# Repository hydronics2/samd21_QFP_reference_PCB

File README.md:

# samd21_QFP_reference_PCB

This is a reference design for a SAMD21 for easy SWD programming and testing.  This layout should work with any SAMD21 QFP package. The QFP package is pretty easy to solder and gives you about the same amount of pins as the original Aruduino 328P. The following SAMD21 packages are QFP:
- SAMD21E15 32kB of Flash **(read this)
- SAMD21E16 64kB of flash **(read this)
- SAMD21E17 128kB of flash
- SAMD21E18 256kB of flash

I made a specific reference board for the SAMD21G [posted here](https://github.com/hydronics2/2020-samd21_QFP_Reference) used in the Adafruit ItsyBitsy M0.

I wanted to start to try SWD programming and these are the less expensive version of the popular SAMD21G on Adafruit and Sparkfun boards.
This PCB design relies heavily on Adafruit and Sparkfun reference design. I realized Adafruit has a similar design for their [32pin Trinket](https://learn.adafruit.com/assets/45723). They do not have a 32.768 crystal or a ferrite bead as recommended by Atmel. Not sure why/how that works. Instead of running the two pins PA00/PA01 to a crystal, they run them to their Dotstar LED!

You can order boards from Oshpark using this link: [project](https://oshpark.com/shared_projects/EjZP7lWQ)

Here's a list of parts:

- ATSAMD21E15B from [digikey](https://www.digikey.com/product-detail/en/microchip-technology/ATSAMD21E15B-AFT/1611-ATSAMD21E15B-AFTCT-ND/6832773). Don't get the ATSAMD21E15L!... the pinout is slightly different.
- generic 10 pin SWD Header from [mouser](https://www.mouser.com/ProductDetail/485-752)
- generic 5.08mm pitch screw headers (or 5mm)
- 	FIXED IND 10UH 500MA 300 MOHM [digikey](https://www.digikey.com/product-detail/en/tdk-corporation/MLZ2012N100LT000/445-6762-1-ND/2523583)
- 3.3V Regulator (18V max input) [mouser](https://www.mouser.com/ProductDetail/511-LDL1117S50R)
- T0-252-3 Mosfet (not needed) [mouser](https://www.mouser.com/ProductDetail/ON-Semiconductor-Fairchild/FDD8780?qs=%2fha2pyFadugI30EyIBTPkO8PumBRFL59Ls98N48NSzc%3d)
- USB micro connector [digikey](https://www.digikey.com/product-detail/en/amphenol-icc-fci/10118194-0001LF/609-4618-1-ND/2785382)
- standard 6mmx6mm tactile button [sparkfun](https://www.sparkfun.com/products/97)
- screw terminal 5mm pitch [sparkfun](https://www.sparkfun.com/products/8432) or [aliexpress](https://www.aliexpress.com/wholesale?catId=0&initiative_id=SB_20190221221755&SearchText=pcb+screw+terminal)
- input protection diodes on the 12V and USB input into the regulator. This is Adafruit's design. [digikey](https://www.digikey.com/product-detail/en/diodes-incorporated/B130-13-F/B130-FDICT-ND/815318)
- 32.768khz crystal (if needed, see above trinket design) [digikey](https://www.digikey.com/product-detail/en/epson/FC-135-32.7680KA-AG3/SER4086DKR-ND/6132726)
- crystal capacitors C7/C8 based on a 7pf load from the above crystal and assumed 2pf stray capacitence, CX1 = CX2 = 2(7pF - 2pF) = 10pF [digikey](https://www.digikey.com/product-detail/en/wurth-electronics-inc/885012006051/732-7793-1-ND/5454420)

SWD Programmer/Debugger: [Segger](https://www.digikey.com/product-detail/en/segger-microcontroller-systems/8.08.91-J-LINK-EDU-MINI/899-1061-ND/7387472)

Notes:
- add a ground plane
- chagne the silkscreen to SAMD21E15
- change the silkscreen C7/C8 from 15pf to 10pf

**READ THIS

The SAMD21E15 only has 32kb of flash. Fine for 8bit architecture but not for 32bit SAMD21 architecture!!
About 50 lines of simple code uses 332 bytes (12%) in for the UNO but compiles over 9,000 bytes (9248 bytes (56%)) for the SAMD21E15, SAMD21E16, SAMD21E17, etc

That means that I should have gone with the SAMD21E17 or SAMD21E18 with 128 or 256kb respectively.

[westf wrote this on the Arduino forum](https://forum.arduino.cc/index.php?topic=602377.msg4091161#msg4091161)... That's not as bad as it sounds - a sketch has a fair about of "fixed overhead" (an empty Zero sketch is 10k.)
So you're seeing THAT rather than some huge "50 lines of code bloats to 9k of code" multiplier for 32bit RISC.   You should be able to fit a pretty significant sketch into the 10k you have left...
But yeah, most ARM libraries (not just the Arduino code, BTW) pretty much assume that you'll have lots of memory, and don't bother being very inefficient.  (adding a tiny bit of floating point will use up another 9k.)
(and 8k for a bootloader?  Sheesh!)

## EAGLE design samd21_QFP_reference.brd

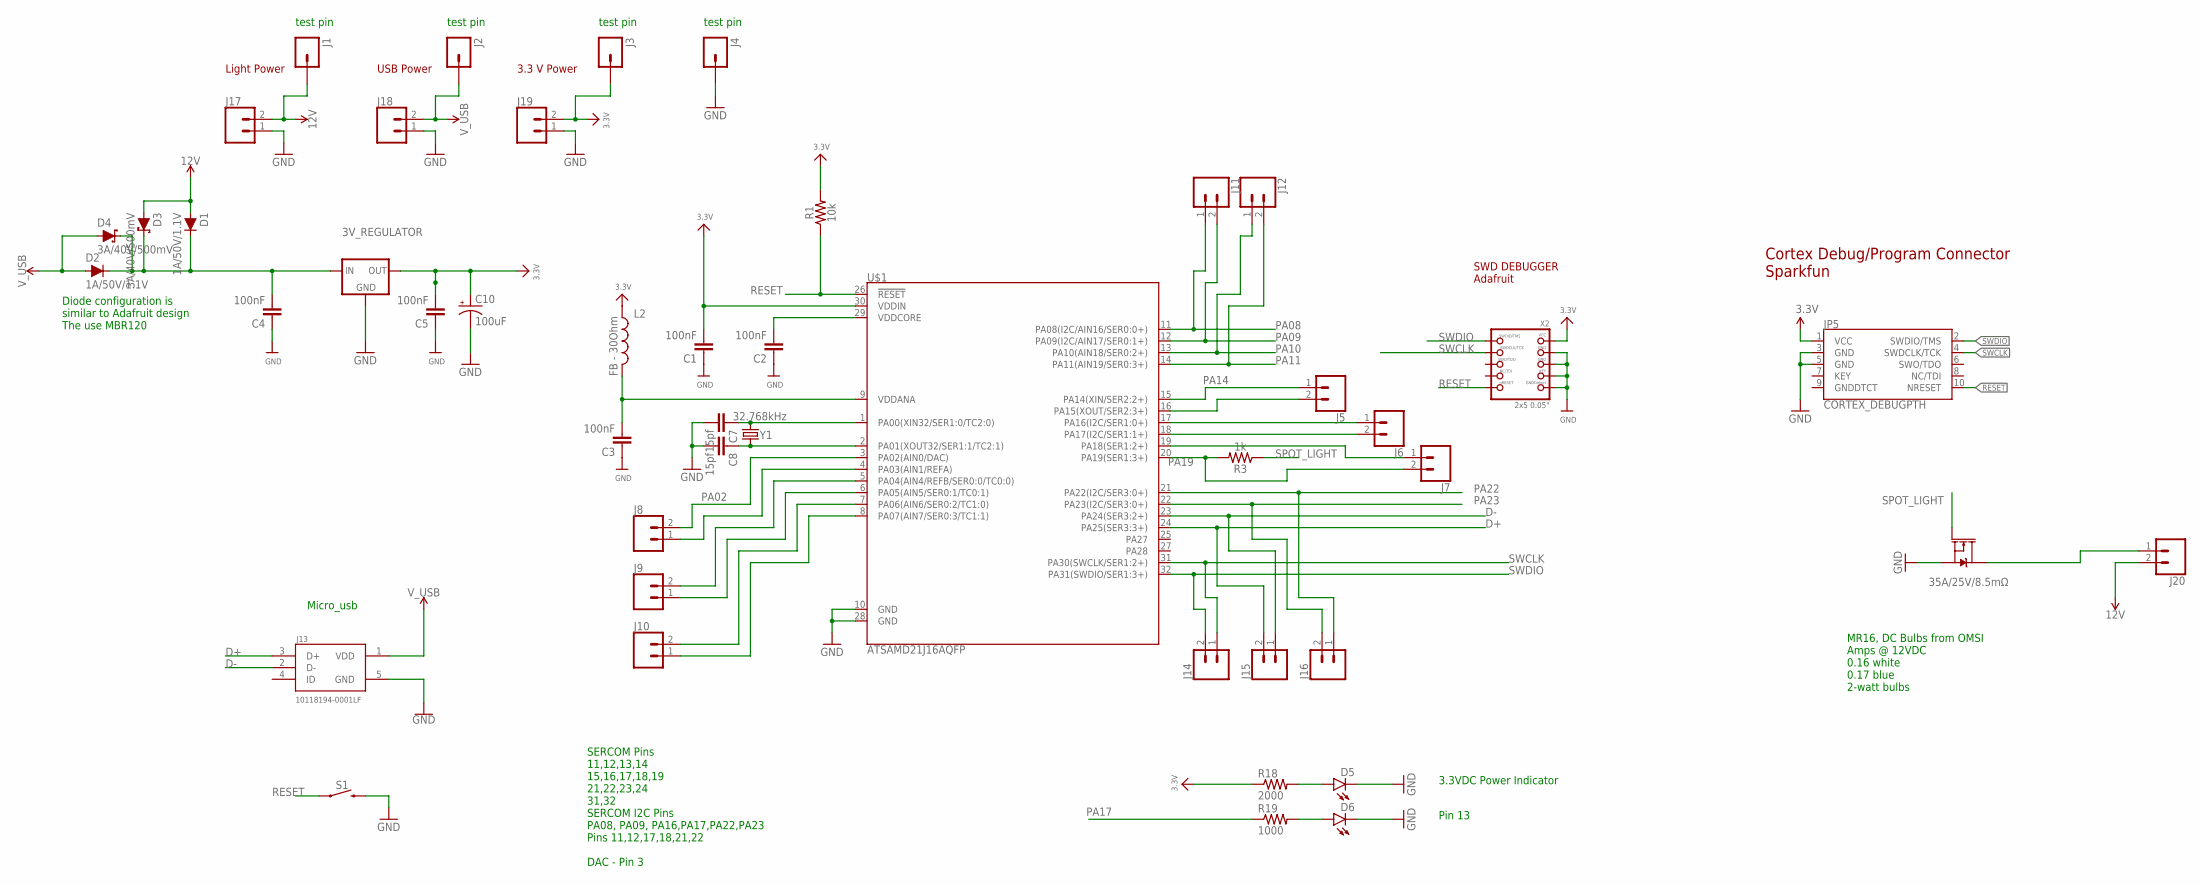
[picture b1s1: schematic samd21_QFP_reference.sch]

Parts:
3V_REGULATOR: LDL1117_5V_REG; SOT223
C1, C2, C3, C4, C5: 100nF; 0805
C7, C8: 15pf; 0805
C10: 100uF; CPOL-RADIAL-2.5MM-6.5MM
D1, D2: 1A/50V/1.1V; DIODE-1N4001
D3, D4: 3A/40V/500mV; SMA-DIODE
D5, D6: LED1206; LED-1206
J1, J2, J3, J4: M01PTH; 1X01
J5, J6, J7, J8, J9, J10, J11, J12, J14, J15, J16, J17, J18, J19, J20: CONN_025MM; SCREWTERMINAL-5MM-2
J13: 10118194-0001LF; FRAMATOME_10118194-0001LF
JP5: CORTEX_DEBUGPTH; 2X5-PTH-1.27MM
L2: FB - 30Ohm; 0805@1
Q1: 35A/25V/8.5mΩ; DPAK
R1: 10k; 0805
R3: 1k; 0805
R18: 2000; 0805
R19: 1000; 0805
S1: MOMENTARY-SWITCH-SPST-PTH-6.0MM-KIT; TACTILE_SWITCH_PTH_6.0MM_KIT
U$1: ATSAMD21J16AQFP; TQFP32-08
X2: 2x5 0.05"; 2X05_1.27MM_BOX_POSTS
Y1: 32.768kHz; CRYSTAL-SMD-3.2X1.5MM

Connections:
3.3V: 3V_REGULATOR.2 (OUT), 3V_REGULATOR.4 (OUT), C1.2, C5.2, C10.1 (+), J3.1, J19.2, JP5.1 (VCC), L2.1, R1.2, R18.1, U$1.30 (VDDIN), X2.1 (VCC)
12V: D1.A, D3.A, J1.1, J17.2, J20.2
D+: J13.3 (D+), J15.2, U$1.24 (PA25(SER3:3+))
D-: J13.2 (D-), J15.1, U$1.23 (PA24(SER3:2+))
GND: 3V_REGULATOR.1 (GND), C1.1, C2.1, C3.1, C4.1, C5.1, C7.2, C8.2, C10.2 (-), D5.C, D6.C, J4.1, J13.5 (GND), J17.1, J18.1, J19.1, JP5.3 (GND), JP5.5 (GND), Q1.3 (S), S1.3 (2), U$1.10 (GND), U$1.28 (GND), X2.3 (GND), X2.5 (GND), X2.7 (KEY), X2.9 (GNDDETECT)
unnamed: C3.2, L2.2, U$1.9 (VDDANA)
unnamed: C7.1, U$1.1 (PA00(XIN32/SER1:0/TC2:0)), Y1.P$2 (2)
unnamed: C2.2, U$1.29 (VDDCORE)
unnamed: C8.1, U$1.2 (PA01(XOUT32/SER1:1/TC2:1)), Y1.P$1 (1)
unnamed: 3V_REGULATOR.3 (IN), C4.2, D1.C, D2.C, D3.C, D4.C
unnamed: J20.1, Q1.4 (D)
unnamed: D5.A, R18.2
unnamed: D6.A, R19.2
PA02: J8.2, U$1.3 (PA02(AIN0/DAC))
PA03: J8.1, U$1.4 (PA03(AIN1/REFA))
PA04: J9.2, U$1.5 (PA04(AIN4/REFB/SER0:0/TC0:0))
PA05: J9.1, U$1.6 (PA05(AIN5/SER0:1/TC0:1))
PA06: J10.2, U$1.7 (PA06(AIN6/SER0:2/TC1:0))
PA07: J10.1, U$1.8 (PA07(AIN7/SER0:3/TC1:1))
PA08: J11.1, U$1.11 (PA08(I2C/AIN16/SER0:0+))
PA09: J11.2, U$1.12 (PA09(I2C/AIN17/SER0:1+))
PA10: J12.1, U$1.13 (PA10(AIN18/SER0:2+))
PA11: J12.2, U$1.14 (PA11(AIN19/SER0:3+))
PA14: J5.1, U$1.15 (PA14(XIN/SER2:2+))
PA15: J5.2, U$1.16 (PA15(XOUT/SER2:3+))
PA16: J6.1, U$1.17 (PA16(I2C/SER1:0+))
PA17: J6.2, R19.1, U$1.18 (PA17(I2C/SER1:1+))
PA18: J7.1, U$1.19 (PA18(SER1:2+))
PA19: J7.2, R3.2, U$1.20 (PA19(SER1:3+))
PA22: J16.1, U$1.21 (PA22(I2C/SER3:0+))
PA23: J16.2, U$1.22 (PA23(I2C/SER3:0+))
RESET: JP5.10 (NRESET), R1.1, S1.1, U$1.26 (!RESET!), X2.10 (NRESET)
SPOT_LIGHT: Q1.1 (G), R3.1
SWCLK: J14.1, JP5.4 (SWDCLK/TCK), U$1.31 (PA30(SWCLK/SER1:2+)), X2.4 (SWDCLK)
SWDIO: J14.2, JP5.2 (SWDIO/TMS), U$1.32 (PA31(SWDIO/SER1:3+)), X2.2 (SWDIO)
V_USB: D2.A, D4.A, J2.1, J13.1 (VDD), J18.2

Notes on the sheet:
SWD DEBUGGER Adafruit
Cortex Debug/Program Connector Sparkfun
SERCOM Pins 11,12,13,14 15,16,17,18,19 21,22,23,24 31,32 SERCOM I2C Pins PA08, PA09, PA16,PA17,PA22,PA23 Pins 11,12,17,18,21,22 DAC - Pin 3
Micro_usb
MR16, DC Bulbs from OMSI Amps @ 12VDC 0.16 white 0.17 blue 2-watt bulbs
Light Power
USB Power
3.3 V Power
Diode configuration is similar to Adafruit design The use MBR120
3.3VDC Power Indicator
Pin 13
test pin

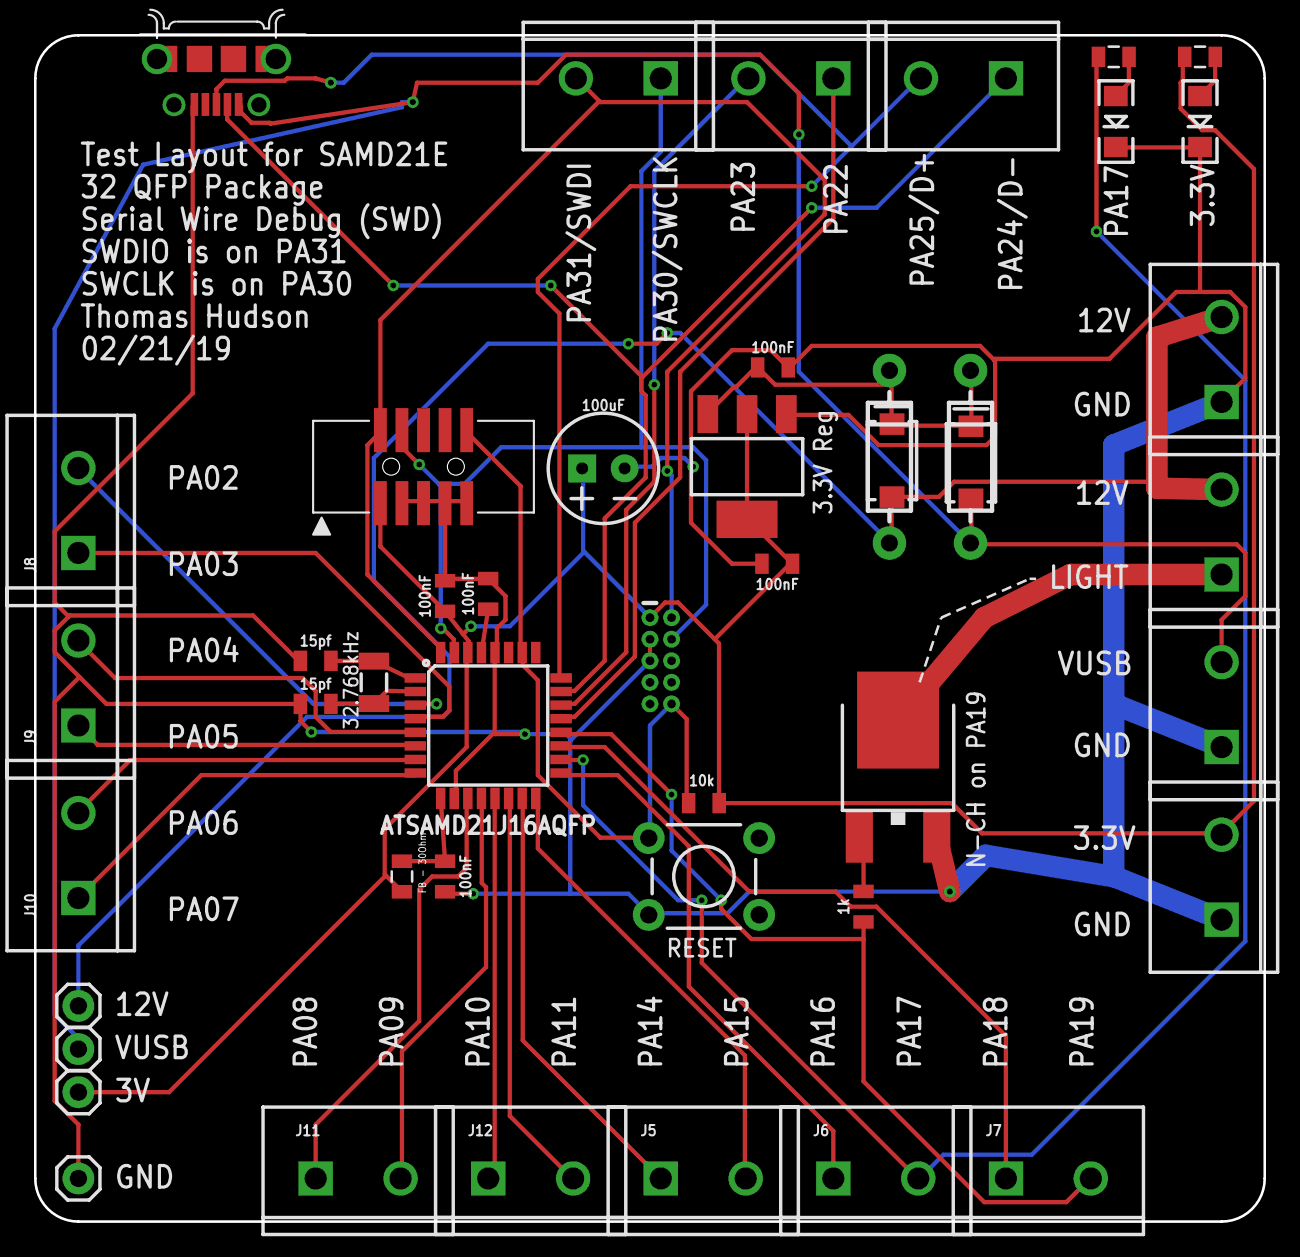
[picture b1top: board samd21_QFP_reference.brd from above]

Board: 2 copper layers, 72.4 x 69.9 mm, 46 parts (0 on the bottom side), 36 nets.

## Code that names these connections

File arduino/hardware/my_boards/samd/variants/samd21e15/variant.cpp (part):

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 * +------------+------------------+--------+-----------------+--------------------------------------------------------------------------------------------------------
 * |            | Digital Low      |        |                 |
 * +------------+------------------+--------+-----------------+--------------------------------------------------------------------------------------------------------
 * | 0          | D0               |  PA04  | D0/A2/SDA/TX    | EIC/EXTINT[4]  ADC/AIN[4]  AC/AIN[0] PTC/Y[2]  SERCOM0/PAD[0]                  *TCC0/WO[0]
 * | 1          | D1               |  PA02  | D1/A0/VOUT      | EIC/EXTINT[2]  ADC/AIN[0] *DAC/VOUT  PTC/Y[0]
 * | 2          | D2               |  PA05  | D2/A1/SCL/RX    | EIC/EXTINT[5]  ADC/AIN[5]  AC/AIN[1] PTC/Y[5]  SERCOM0/PAD[1]                  *TCC0/WO[1]
 * | 3          | Dotstar Data     |  PA00  |                 |
 * | 4          | DotStar Clock    |  PA01  |                 |
 * +------------+------------------+--------+-----------------+--------------------------------------------------------------------------------------------------------
 * |            | USB              |        |                 |
 * +------------+------------------+--------+-----------------+--------------------------------------------------------------------------------------------------------
 * | 5          |                  |  PA28  | USB_HOST_ENABLE | EIC/EXTINT[8]
 * | 6          |                  |  PA24  | USB_NEGATIVE    | *USB/DM
 * | 7          |                  |  PA25  | USB_POSITIVE    | *USB/DP
 * +------------+------------------+--------+-----------------+--------------------------------------------------------------------------------------------------------
 * |            | Analog Pins      |        |                 |
 * +------------+------------------+--------+-----------------+--------------------------------------------------------------------------------------------------------
 * | 8          | A0               |  PA02  | D1/A0/VOUT      | EIC/EXTINT[2] *ADC/AIN[0]  DAC/VOUT  PTC/Y[0]
 * | 9          | A1               |  PA05  | D2/A1/SCL/RX    | EIC/EXTINT[5] *ADC/AIN[5]  AC/AIN[1] PTC/Y[5]  SERCOM0/PAD[1]                  TCC0/WO[1]
 * | 10         | A2               |  PA04  | D0/A2/SDA/TX    | EIC/EXTINT[4] *ADC/AIN[4]  AC/AIN[0] PTC/Y[2]  SERCOM0/PAD[0]                  TCC0/WO[0]
 * +------------+------------------+--------+-----------------+--------------------------------------------------------------------------------------------------------
 * |            | SWD              |        |                 |
 * +------------+------------------+--------+-----------------+--------------------------------------------------------------------------------------------------------
 * | 11         |                  |  PA30  | SWD Clock       |
 * | 12         |                  |  PA31  | SWD Data        |
 * +------------+------------------+--------+-----------------+--------------------------------------------------------------------------------------------------------
 * |            | Digital High     |        |                 |
 * +------------+------------------+--------+-----------------+--------------------------------------------------------------------------------------------------------
 * | 13         | 13               |  PA23  | LED             | EIC/EXTINT[7]                        PTC/X[11] *SERCOM3/PAD[1] SERCOM5/PAD[1] TC4/WO[1] TCC0/WO[5]
 * | 14         | 14               |  PA10  | RXLED           | EIC/EXTINT[10] ADC/AIN[18]           PTC/X[2] *SERCOM0/PAD[2]                  TCC0/WO[2]  TCC1/WO[0]
 * | 15         | 15               |  PA11  | TXLED           | EIC/EXTINT[11] ADC/AIN[19]           PTC/X[3] *SERCOM0/PAD[3]  SERCOM2/PAD[3]  TCC0/WO[3]  TCC1/WO[1]
 * +------------+------------------+--------+-----------------+--------------------------------------------------------------------------------------------------------
 */

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
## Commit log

2019-03-10 update board files
2019-03-10 added all hardware Signed-off-by: thomas <hydronics@gmail.com>
2020-06-03 added cross link.. fixed link to header

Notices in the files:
arduino/hardware/my_boards/samd/variants/samd21e15/variant.cpp:
Copyright (c) 2014-2015 Arduino LLC.  All right reserved.
parts and their libraries:
microbuilder: This work is placed in the public domain, and may be freely used for commercial and non-commercial work with the following conditions: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
SparkFun-Resistors: Licensing: Creative Commons ShareAlike 4.0 International - https://creativecommons.org/licenses/by-sa/4.0
